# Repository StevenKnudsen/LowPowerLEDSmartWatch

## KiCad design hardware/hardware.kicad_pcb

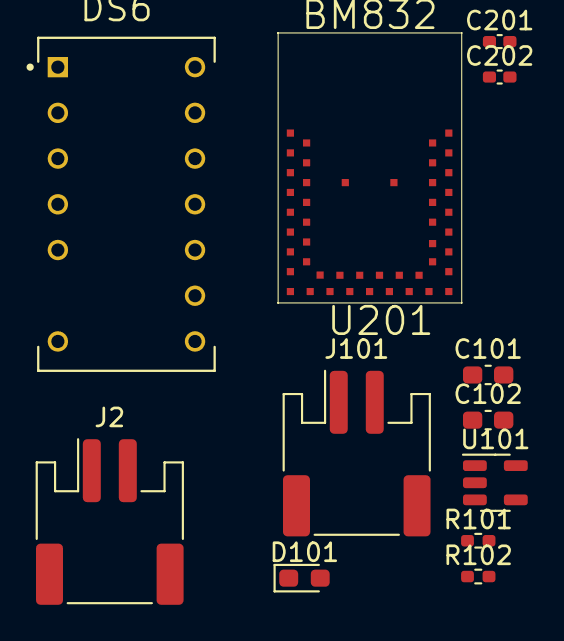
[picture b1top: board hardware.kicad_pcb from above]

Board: 2 copper layers, 12 parts (0 on the bottom side), 6 nets, no tracks yet.

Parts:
C101, C102: 10u; C_0603_1608Metric_Pad1.08x0.95mm_HandSolder
C201, C202: 12p; C_0402_1005Metric_Pad0.74x0.62mm_HandSolder
D101: Yellow; LED_0603_1608Metric_Pad1.05x0.95mm_HandSolder
DS6: LTP-305G; DIP762W50P254L1875H400Q13
J2: Conn_01x02; JST_PH_S2B-PH-SM4-TB_1x02-1MP_P2.00mm_Horizontal
J101: Battery; JST_PH_S2B-PH-SM4-TB_1x02-1MP_P2.00mm_Horizontal
R101: 470; R_0402_1005Metric_Pad0.72x0.64mm_HandSolder
R102: 5k1; R_0402_1005Metric_Pad0.72x0.64mm_HandSolder
U101: MCP73831-2-OT; SOT-23-5
U201: BM832; BM832-1-BM832

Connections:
+5V: C102.2, D101.2 (A), U101.4 (V_{DD})
+BATT: C101.2, J101.1, U101.3 (V_{BAT})
GND: C101.1, C102.1, J101.2, R102.2, U101.2 (V_{SS})
unnamed: D101.1 (K), R101.1
unnamed: R102.1, U101.5 (PROG)
nBatteryCharging: R101.2, U101.1 (STAT)

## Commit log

2023-02-13 SmartWatch Block Diagram.drawio
2023-02-13 rename block diagram file
2023-02-19 make docs dir; make hardware dir for KiCAD
2023-02-19 don't keep KiCAD backup zip files
2023-07-05 some power and ble additions to schematic
